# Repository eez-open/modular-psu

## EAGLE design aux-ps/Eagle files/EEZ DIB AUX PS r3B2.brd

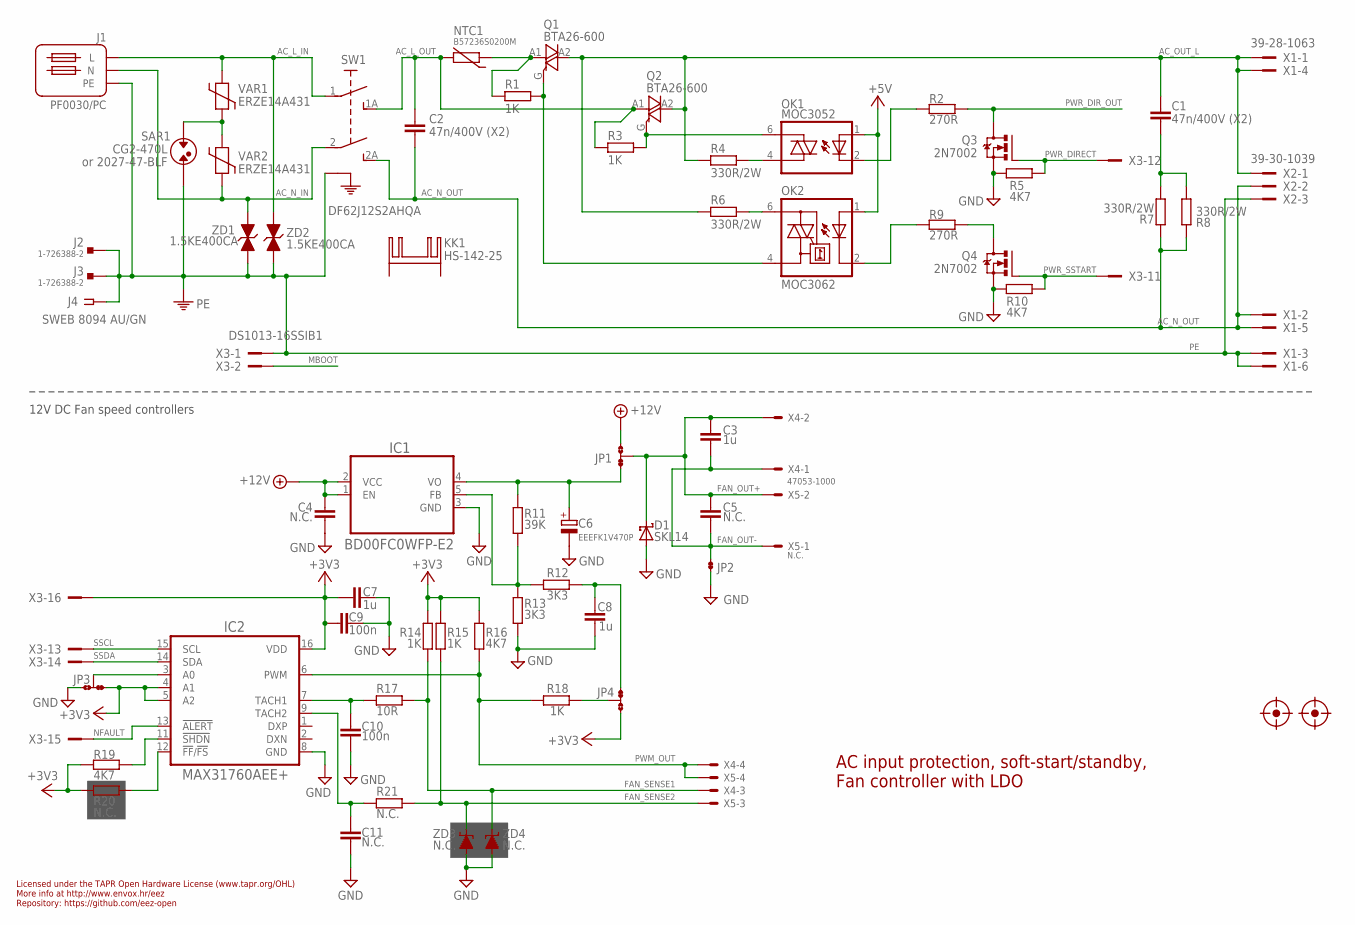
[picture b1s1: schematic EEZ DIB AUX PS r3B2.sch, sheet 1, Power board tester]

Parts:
C1, C2: 47n/400V (X2); C102-054X133
C3, C7, C8: 1u; C0805
C4, C5: N.C.; C0805
C6: EEEFK1V470P; CAPAE660X610N
C9, C10: 100n; C0603
C11: N.C.; C0603
D1: SKL14; SOD123
FM1, FM2: FIDUCIAL
IC1: BD00FC0WFP-E2; TO-252-5
IC2: MAX31760AEE+; DBQ16
J1: PF0030/PC
J2, J3: 1-726388-2; PCB_TAB-4.8MM
J4: SWEB 8094 AU/GN; S16N-PC
JP1, JP3, JP4: JP3-CUT
JP2: JP2-NOCUT
KK1: HS-142-25; SK129
NTC1: B57236S0200M; NTC_11.5X6_RM5
OK1: MOC3052; DIL6-SMD
OK2: MOC3062; DIL6-SMD; MPN MOC3033S-M
Q1, Q2: BTA26-600; TOP3S-1
Q3, Q4: 2N7002; SOT103P240X110-3N
R1, R3, R14, R15, R18: 1K; R0805
R2, R9: 270R; R0805
R4, R6, R7, R8: 330R/2W; R2512
R5, R10, R16, R19: 4K7; R0805
R11: 39K; R0805
R12, R13: 3K3; R0805
R17: 10R; R0805
R20, R21: N.C.; R0805
SAR1: CG2-470L; SAR
SW1: DF62J12S2AHQA; DF62J12S2
VAR1, VAR2: ERZE14A431; VARISTOR_13MM
X1: 39-28-1063; MINIFIT_5566-06A_CRE
X2: 39-30-1039; MINIFIT_39301039_CRE
X3: DS1013-16SSIB1; IDC-16PIN
X4: 47053-1000
X5: N.C.; 47053-1000
ZD1, ZD2: 1.5KE400CA; DO201-BIDIR
ZD3, ZD4: N.C.; SOD123

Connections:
12V_PWM: C6.1 (+), IC1.4 (VO), JP1.NC, R11.1
+3V3: C7.2, C9.2, IC2.4 (A1), IC2.5 (A2), IC2.16 (VDD), JP3.NC, JP4.NO, R14.2, R15.2, R16.2, R19.2, R20.2, X3.16; also elsewhere on the board
+5V: OK1.1 (A), OK2.1 (A); also elsewhere on the board
+12V: C4.1, IC1.1 (EN), IC1.2 (VCC), JP1.NO; also elsewhere on the board
AC_L_IN: J1.L, SW1.1, VAR1.2, ZD2.A (2)
AC_L_OUT: C2.1, NTC1.1, Q2.A1, R3.2, SW1.1A (S); also elsewhere on the board
AC_N_IN: J1.N, SW1.2 (P1), VAR2.1, ZD1.A (2)
AC_N_OUT: C2.2, R7.1, R8.1, SW1.2A (S1), X1.2, X1.5, X2.2; also elsewhere on the board
AC_OUT_L: C1.1, Q1.A2, Q2.A2, R4.2, R6.2, X1.1, X1.4, X2.1
FAN_OUT+: C3.1, C5.1, D1.C, JP1.COM, X4.2, X5.2
FAN_OUT-: C3.2, C5.2, JP2.2, X4.1, X5.1
FAN_SENSE1: R14.1, R17.2, X4.3, ZD4.C
FAN_SENSE2: R15.1, R21.2, X5.3, ZD3.C
GND: C4.2, C6.2 (-), C7.1, C8.2, C9.1, C10.2, C11.2, D1.A, IC1.3 (GND), IC2.8 (GND), JP2.1, JP3.NO, Q3.2 (S), Q4.2 (S), R5.1, R10.1, R13.2, ZD3.A, ZD4.A; also elsewhere on the board
LDO_FB: IC1.5 (FB), R11.2, R12.1, R13.1
MBOOT: X3.2; also elsewhere on the board
unnamed: NTC1.2, Q1.A1, R1.1
unnamed: C10.1, IC2.7 (TACH1), R17.1
unnamed: IC2.12 (!FF!/!FS!), R20.1
unnamed: JP4.COM, R18.1
unnamed: SAR1.P$1, VAR1.1, VAR2.2
unnamed: OK2.2 (C), R9.1
unnamed: C8.1, JP4.NC, R12.2
unnamed: OK1.2 (C), R2.1
unnamed: Q4.3 (D), R9.2
unnamed: IC2.11 (!SHDN), R19.1
unnamed: C11.1, IC2.9 (TACH2), R21.1
unnamed: IC2.3 (A0), JP3.COM
unnamed: OK1.6 (A2), Q2.G, R3.1
unnamed: OK2.4 (A1), Q1.G, R1.2
unnamed: OK2.6 (A2), R6.1
unnamed: OK1.4 (A1), R4.1
unnamed: C1.2, R7.2, R8.2
NFAULT: IC2.13 (!ALERT), X3.15
PE: J1.PE, J2.1, J2.2, J3.1, J3.2, J4.1, J4.NC1, J4.NC2, J4.NC3, J4.NC4, SAR1.P$2, SW1.PE1 (PE), SW1.PE2 (PE), X1.3, X1.6, X2.3, X3.1, ZD1.C (1), ZD2.C (1)
PWM_OUT: IC2.6 (PWM), R16.1, R18.2, X4.4, X5.4
PWR_DIRECT: Q3.1 (G), R5.2, X3.12
PWR_DIR_OUT: Q3.3 (D), R2.2; also elsewhere on the board
PWR_SSTART: Q4.1 (G), R10.2, X3.11
SSCL: IC2.15 (SCL), X3.13
SSDA: IC2.14 (SDA), X3.14

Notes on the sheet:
Licensed under the TAPR Open Hardware License (www.tapr.org/OHL)
Repository: https://github.com/eez-open
More info at http://www.envox.hr/eez
or 2027-47-BLF
12V DC Fan speed controllers
AC input protection, soft-start/standby, Fan controller with LDO

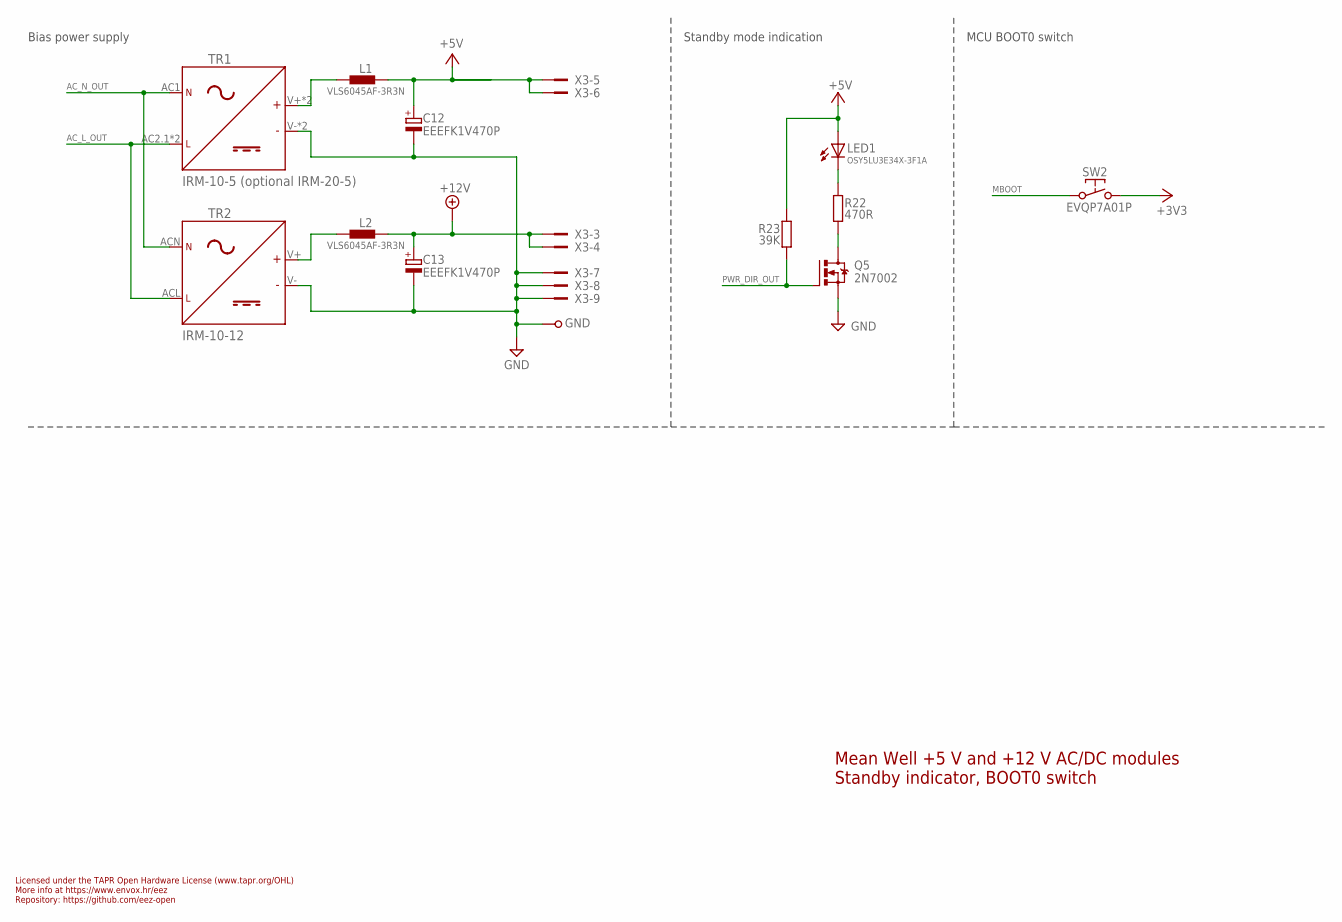
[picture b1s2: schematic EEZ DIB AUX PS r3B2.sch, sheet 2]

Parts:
C12, C13: EEEFK1V470P; CAPAE660X610N
GND: PCB_TEST_TABSHIELD; PCB_SHIELD_TAB
L1, L2: VLS6045AF-3R3N; COILCRAFT_HPI0630
LED1: OSY5LU3E34X-3F1A; OSG8
Q5: 2N7002; SOT103P240X110-3N; MPN 2N7002-7-F
R22: 470R; R0805
R23: 39K; R0805
SW2: EVQP7A01P; PANASONIC_EVQP
TR1: IRM-10-5 (optional IRM-20-5); IRM-10/20_COMBO
TR2: IRM-10-12; IRM-10
X3: DS1013-16SSIB1; IDC-16PIN

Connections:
+3V3: SW2.2.1 (2), SW2.2.2 (2); also elsewhere on the board
+5V: C12.1 (+), L1.2, LED1.A, R23.1, X3.5, X3.6; also elsewhere on the board
+12V: C13.1 (+), L2.2, X3.3, X3.4; also elsewhere on the board
AC_L_OUT: TR1.AC2.1 (AC/L), TR1.AC2.2 (AC/L), TR2.ACL (AC/L); also elsewhere on the board
AC_N_OUT: TR1.AC1 (AC/N), TR2.ACN (AC/N); also elsewhere on the board
GND: C12.2 (-), C13.2 (-), GND.1, Q5.2 (S), TR1.V- (-), TR1.V-1 (-), TR2.V- (-), X3.7, X3.8, X3.9; also elsewhere on the board
MBOOT: SW2.1.1 (1), SW2.1.2 (1); also elsewhere on the board
unnamed: L2.1, TR2.V+ (+)
unnamed: Q5.3 (D), R22.2
unnamed: LED1.C, R22.1
unnamed: L1.1, TR1.V+ (+), TR1.V+1 (+)
PWR_DIR_OUT: Q5.1 (G), R23.2; also elsewhere on the board

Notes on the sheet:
Licensed under the TAPR Open Hardware License (www.tapr.org/OHL)
Repository: https://github.com/eez-open
More info at https://www.envox.hr/eez
Mean Well +5 V and +12 V AC/DC modules Standby indicator, BOOT0 switch
Standby mode indication
MCU BOOT0 switch
Bias power supply

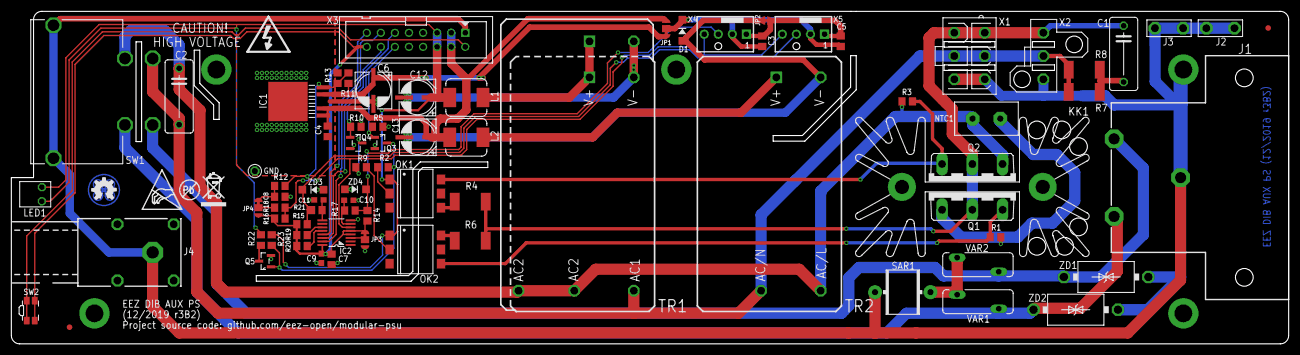
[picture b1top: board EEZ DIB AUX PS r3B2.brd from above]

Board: 2 copper layers, 230.5 x 60.0 mm, 82 parts (0 on the bottom side), 45 nets.

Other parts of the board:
EEZ_SIGNATURE: SIGNATURESMALL; SIGNATURE_5MM
U$2: PB_SMALL
U$3: RECYCLE_BIN1/8
U$4: ESD_SYMBOL

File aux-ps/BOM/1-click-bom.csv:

References,Qty,Description,Manufacturer,MPN,Digikey,Mouser,RS,Newark,Farnell
"ZD1, ZD2",2,1.5KE400CA,,1.5KE400CARL,1.5KE400CA-TPMSCT-ND,8331.5KE400CATP,1.5KE400CA,,1.5KE400CARL
X4; fan connector,1,22-27-2031,,22-27-2031,WM4112-ND,53822272031,22272031,,22272031
X3,1,DS1013-16SSIB1,,MC-254-16-00-ST-DIP,ED10523-ND,71061201621621,61201621621,,MC2541600STDIP
X2,1,39-30-1039,,39-30-1039,WM18442-ND,53839301039,39301039,,39301039
X1,1,39-28-1063,,39-28-1063,WM3802-ND,53839281063,39281063,,39281063
"VAR1, VAR2",2,ERZE14A431 or V275LA20AP,,ERZE11A431,P16688-ND,667ERZE11A431,ERZE11A431,,ERZE11A431
TR2,1,IRM-10-12,,IRM-10-12,1866-3028-ND,709IRM1012,IRM1012,,IRM1012
TR1,1,IRM-10-5,,IRM-10-5,1866-3032-ND,709IRM105,IRM105,,IRM105
SW2,1,EVQP7A01P,,EVQP7A01P,P16763CT-ND,667EVQP7A01P,EVQP7A01P,,EVQP7A01P
SW1,1,DF62J12S2AHQA,,DF62J12S2AHQA,CKN2062-ND,611DF62J12S2AHQA,DF62J12S2AHQA,,DF62J12S2AHQA
SAR1,1,CG2-470L,,2027-47-BLF,2027-47-BLF-ND,652202747BLF,CG2470L,,202747BLF
"R5, R10, R16, R19",4,4K7,,CRGCQ0805F4K7,311-4.70KCRCT-ND,603RC0805FR074K7L,CRG0805F4K7,,CRGCQ0805F4K7
"R4, R6, R7, R8",4,330R/2W,,3520330RJT,RMCF2512JT330RCT-ND,2793520330RJT,3521330RFT,,3520330RJT
R22,1,470R,,WCR0805-470RFI,311-470CRCT-ND,71CRCW0805470RFKEB,CRG0805F470R,,WCR0805470RFI
"R2, R9",2,270R,,MCMR08X271 JTL,RMCF0805FT270RCT-ND,652CR0805FX2700ELF,CRG0805F270R,,MCMR08X271 JTL
R17,1,10R,,RC1206FR-0710RL,311-10.0CRCT-ND,603RC1206FR0710RL,CR1206FX10R0ELF,,RC1206FR0710RL
"R1, R3, R14, R15, R18",5,1K,,WCR0805-1K0FI,RC0805FR-071KL,603RC0805FR071KL,CRG0805F1K0,,WCR08051K0FI
"R12, R13",2,3K3,,MCWR08X3301FTL,A129755CT-ND,,CRG0805F3K3,,MCWR08X3301FTL
"R11, R23",2,39K,,MCWR08X3902FTL,RMCF0805FT39K0CT-ND,652CR0805FX3902ELF,CRCW080539K0FKEA,,MCWR08X3902FTL
"Q3, Q4, Q5",3,2N7002,,2N7002-7-F,2N7002LT1GOSCT-ND,8632N7002LT1G,2N7002LT1G,,2N70027F
"Q1, Q2",2,BTA26-600,,BTA26-600BRG,497-2427-5-ND,511BTA26600B,BTA26600BRG,,BTA26600BRG
OK2,1,MOC3062,,MOC3062SR2VM,MOC3062SM-ND,512MOC3062SM,MOC3062SM,,MOC3062SR2VM
OK1,1,MOC3052,,MOC3052SM,MOC3052SM-ND,512MOC3052SM,MOC3052SM,,MOC3052SM
NTC1,1,B57236S0200M,,B57236S0200M,495-3047-ND,871B57236S200M,,,B57236S0200M
LED1,1,OSY5LU3E34X-3F1A,,,-,,,,
"L1, L2",2,VLS6045AF-3R3N,,IHLP2020CZER3R3M11,445-180834-1-ND,810VLS6045AF3R3N,,,IHLP2020CZER3R3M11
J4,1,SWEB 8094 AU/GN,,,-,,,,
"J2, J3",2,1-726388-2,,1-726388-2,A121493-ND,5717263882,17263882,,17263882
J1,1,PF0030/PC,,PF0030/PC,708-1914-ND,161PF0030/PC,PF0030/PC,,PF0030/PC
IC2,1,MAX31760AEE+,,MAX31760AEE+,MAX31760AEE+-ND,700MAX31760AEE+,,,MAX31760AEE+
IC1,1,BD00FC0WFP-E2,,BD00FC0WFP-E2,BD00FC0WFP-E2CT-ND,755BD00FC0WFPE2,BD00FC0WFPE2,,BD00FC0WFPE2
D1,1,SKL14,,PMEG4010EGWX,1727-7335-1-ND,841PMEG4010EGWX,PMEG4010EGWX,,PMEG4010EGWX
"C9, C10",2,100n,,C0603C104K4RAC7081,490-4774-1-ND,80C0603C104M4R,VJ0603Y104KXJAT,,C0603C104K4RAC7081
"C6, C12, C13",3,EEEFK1V470P,,EEEFK1V470P,PCE3842CT-ND,667EEEFK1V470P,EEEFK1V470P,,EEEFK1V470P
"C3, C7, C8",3,1u,,VJ0805Y105KXXTW1BC,587-1283-1-ND,603CC805MKX7R7BB105,C0805C105K4RACTU,,VJ0805Y105KXXTW1BC
"C1, C2",2,47n/400V (X2),,B32921C3473K000,399-11478-ND,871B32921C3473K,B32921C3473M000,,B32921C3473K000

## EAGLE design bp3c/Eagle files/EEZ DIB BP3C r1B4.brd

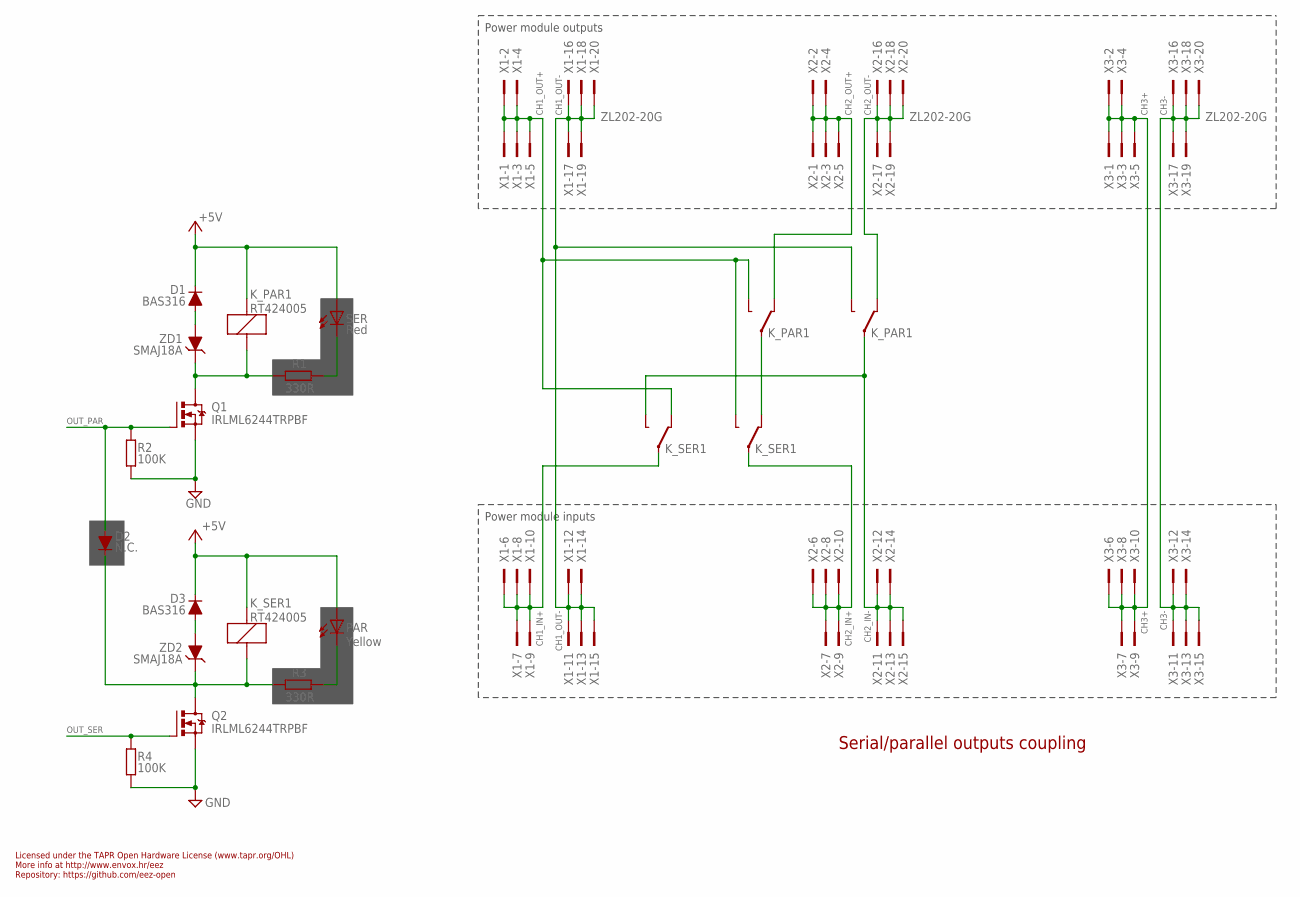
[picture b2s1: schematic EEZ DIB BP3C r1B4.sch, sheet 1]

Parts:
D1, D3: BAS316; SOD323-R
D2: N.C.; SOD323-R
K_PAR1: RT424005; RT-C/016A5_ROUND
K_SER1: RT424005; RT-C/016A5_ROUND
PAR: Yellow; LED_0805
Q1, Q2: IRLML6244TRPBF; SOT103P240X110-3N; MPN 2N7002-7-F
R1, R3: 330R; R0805
R2, R4: 100K; R0805
SER: Red; LED_0805
X1, X2, X3: ZL202-20G; DS1021-2*10SF11
ZD1, ZD2: SMAJ18A; DO214AC

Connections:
+5V: D1.C, D3.C, K_PAR1.A2 (C1), K_SER1.A2 (C1), PAR.A, SER.A; also elsewhere on the board
CH1_IN+: K_SER1.11A, X1.6, X1.7, X1.8, X1.9, X1.10
CH1_OUT+: K_PAR1.14A (O), K_SER1.12A (S), K_SER1.14B (O), X1.1, X1.2, X1.3, X1.4, X1.5
CH1_OUT-: K_PAR1.14B (O), X1.11, X1.12, X1.13, X1.14, X1.15, X1.16, X1.17, X1.18, X1.19, X1.20
CH2_IN+: K_SER1.11B, X2.6, X2.7, X2.8, X2.9, X2.10
CH2_IN-: K_PAR1.11B, K_SER1.14A (O), X2.11, X2.12, X2.13, X2.14, X2.15
CH2_OUT+: K_PAR1.12A (S), X2.1, X2.2, X2.3, X2.4, X2.5
CH2_OUT-: K_PAR1.12B (S), X2.16, X2.17, X2.18, X2.19, X2.20
CH3+: X3.1, X3.2, X3.3, X3.4, X3.5, X3.6, X3.7, X3.8, X3.9, X3.10
CH3-: X3.11, X3.12, X3.13, X3.14, X3.15, X3.16, X3.17, X3.18, X3.19, X3.20
GND: Q1.2 (S), Q2.2 (S), R2.1, R4.1; also elsewhere on the board
unnamed: K_PAR1.11A, K_SER1.12B (S)
unnamed: PAR.C, R3.1
unnamed: R1.1, SER.C
unnamed: D2.C, K_SER1.A1 (C2), Q2.3 (D), R3.2, ZD2.C
unnamed: K_PAR1.A1 (C2), Q1.3 (D), R1.2, ZD1.C
unnamed: D3.A, ZD2.A
unnamed: D1.A, ZD1.A
OUT_PAR: D2.A, Q1.1 (G), R2.2; also elsewhere on the board
OUT_SER: Q2.1 (G), R4.2; also elsewhere on the board

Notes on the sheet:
Licensed under the TAPR Open Hardware License (www.tapr.org/OHL)
Repository: https://github.com/eez-open
More info at http://www.envox.hr/eez
Serial/parallel outputs coupling
Power module inputs
Power module outputs

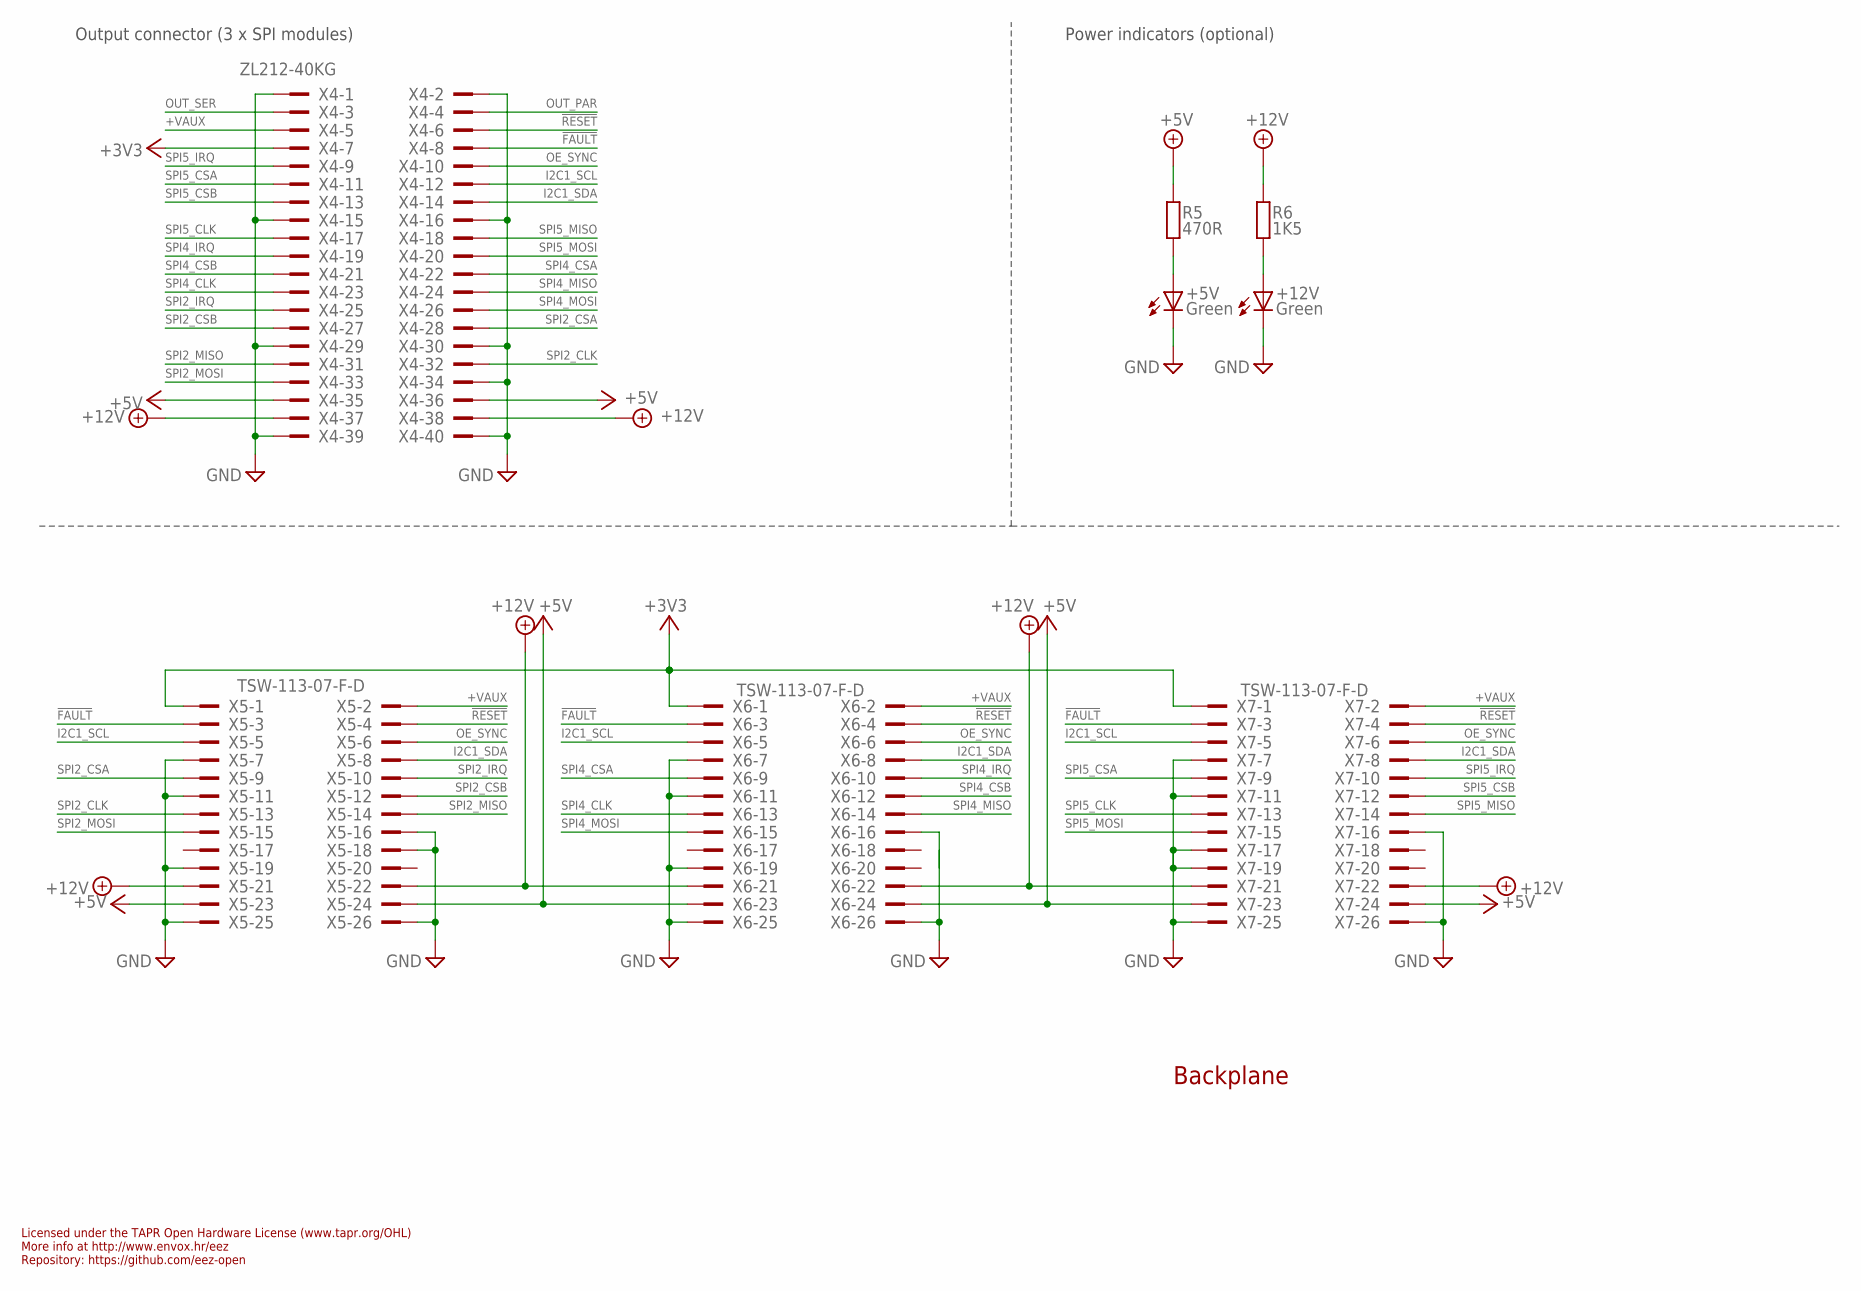
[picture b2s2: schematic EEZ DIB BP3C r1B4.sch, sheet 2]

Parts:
+5V, +12V: Green; LED_0805
R5: 470R; R0805
R6: 1K5; R0805
X4: ZL212-40KG
X5, X6, X7: TSW-113-07-F-D

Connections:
!FAULT: X4.8, X5.3, X6.3, X7.3
!RESET: X4.6, X5.4, X6.4, X7.4
+3V3: X4.7, X5.1, X6.1, X7.1
+5V: R5.1, X4.35, X4.36, X5.23, X5.24, X6.23, X6.24, X7.23, X7.24; also elsewhere on the board
+12V: R6.1, X4.37, X4.38, X5.21, X5.22, X6.21, X6.22, X7.21, X7.22
+VAUX: X4.5, X5.2, X6.2, X7.2
GND: +5V.C, +12V.C, X4.1, X4.2, X4.15, X4.16, X4.29, X4.30, X4.34, X4.39, X4.40, X5.7, X5.11, X5.16, X5.18, X5.19, X5.25, X5.26, X6.7, X6.11, X6.16, X6.19, X6.25, X6.26, X7.7, X7.11, X7.16, X7.17, X7.19, X7.25, X7.26; also elsewhere on the board
I2C1_SCL: X4.12, X5.5, X6.5, X7.5
I2C1_SDA: X4.14, X5.8, X6.8, X7.8
unnamed: +5V.A, R5.2
unnamed: +12V.A, R6.2
OE_SYNC: X4.10, X5.6, X6.6, X7.6
OUT_PAR: X4.4; also elsewhere on the board
OUT_SER: X4.3; also elsewhere on the board
SPI2_CLK: X4.32, X5.13
SPI2_CSA: X4.28, X5.9
SPI2_CSB: X4.27, X5.12
SPI2_IRQ: X4.25, X5.10
SPI2_MISO: X4.31, X5.14
SPI2_MOSI: X4.33, X5.15
SPI4_CLK: X4.23, X6.13
SPI4_CSA: X4.22, X6.9
SPI4_CSB: X4.21, X6.12
SPI4_IRQ: X4.19, X6.10
SPI4_MISO: X4.24, X6.14
SPI4_MOSI: X4.26, X6.15
SPI5_CLK: X4.17, X7.13
SPI5_CSA: X4.11, X7.9
SPI5_CSB: X4.13, X7.12
SPI5_IRQ: X4.9, X7.10
SPI5_MISO: X4.18, X7.14
SPI5_MOSI: X4.20, X7.15

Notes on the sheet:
Licensed under the TAPR Open Hardware License (www.tapr.org/OHL)
Repository: https://github.com/eez-open
More info at http://www.envox.hr/eez
Backplane
Output connector (3 x SPI modules)
Power indicators (optional)

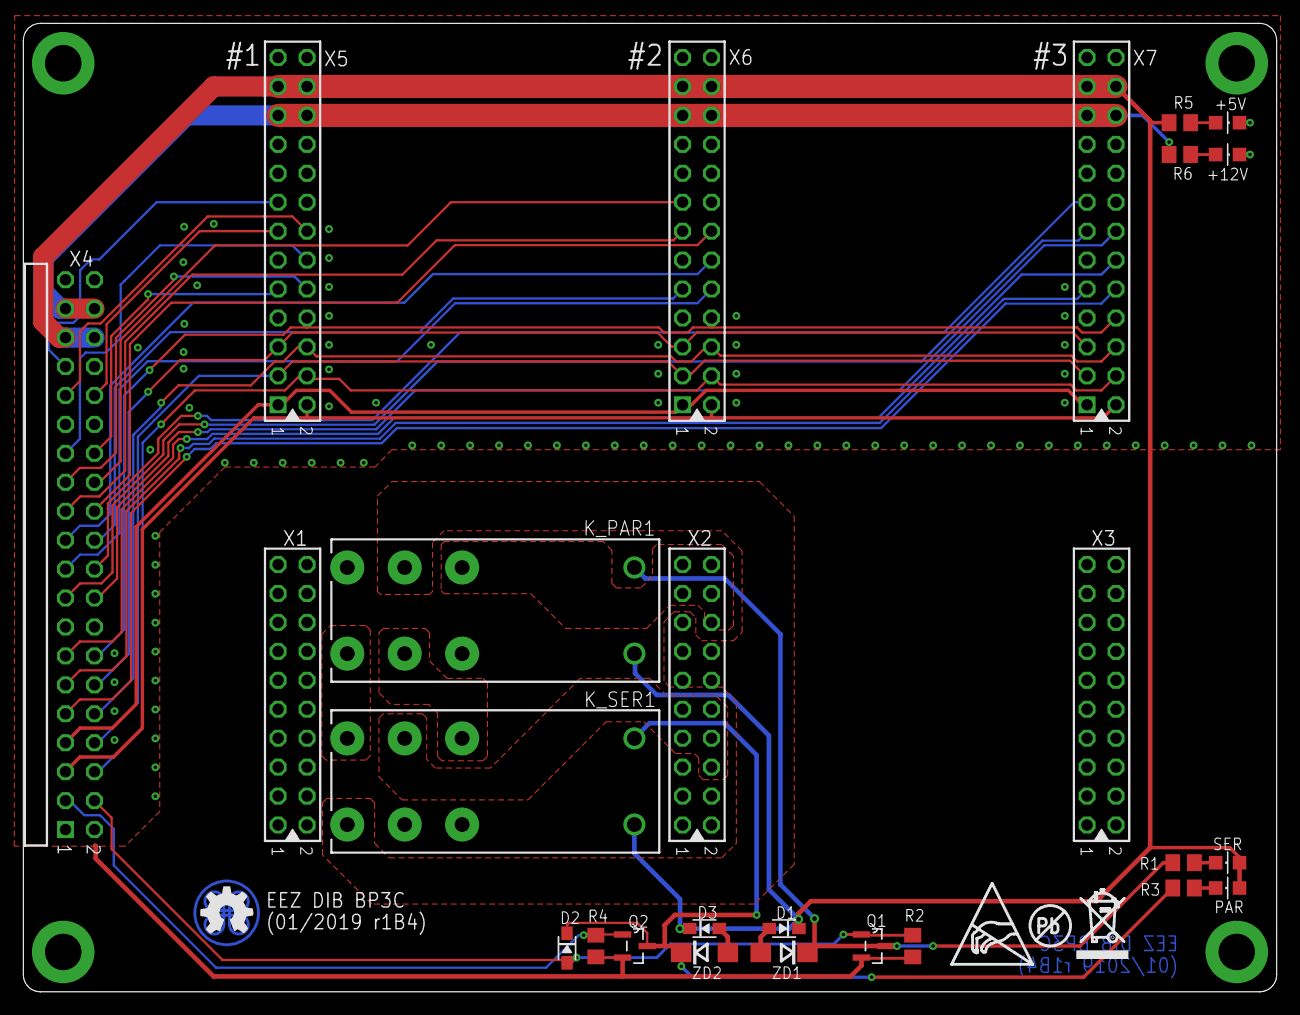
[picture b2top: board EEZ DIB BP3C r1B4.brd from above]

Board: 2 copper layers, 110.0 x 85.0 mm, 30 parts (0 on the bottom side), 48 nets.

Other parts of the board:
EEZ_SIGNATURE: SIGNATURESMALL; SIGNATURE_5MM
U$2: RECYCLE_BIN1/8
U$4: ESD_SYMBOL
U$5: PB_SMALL

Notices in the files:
parts and their libraries:
EEZ_DIB: This work is licensed under the TAPR Open Hardware License.
